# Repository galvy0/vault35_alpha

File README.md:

# Vault35 Alpha Stagger PCB
Alpha stagger version of Cain's Vault35 keyboard.  
Check out the original product and other awesome projects of Cain at [https://mechvault.net/](https://mechvault.net/).  

## PCB
### Layout Options

### Middle Column Options
There are four options to fill in the space in the middle column: 1) two normal switches, 2) two encoders (or a combination of encoders and normal switches), 3) an OLED, and 4) a trackpoint module.  
For TP option, refer to my phoenix45 alpha stagger repo: https://github.com/galvy0/phoenix45_alpha

## Firmware
https://github.com/galvy0/qmk_firmware/tree/galvy/keyboards/galvy/vault35_alpha

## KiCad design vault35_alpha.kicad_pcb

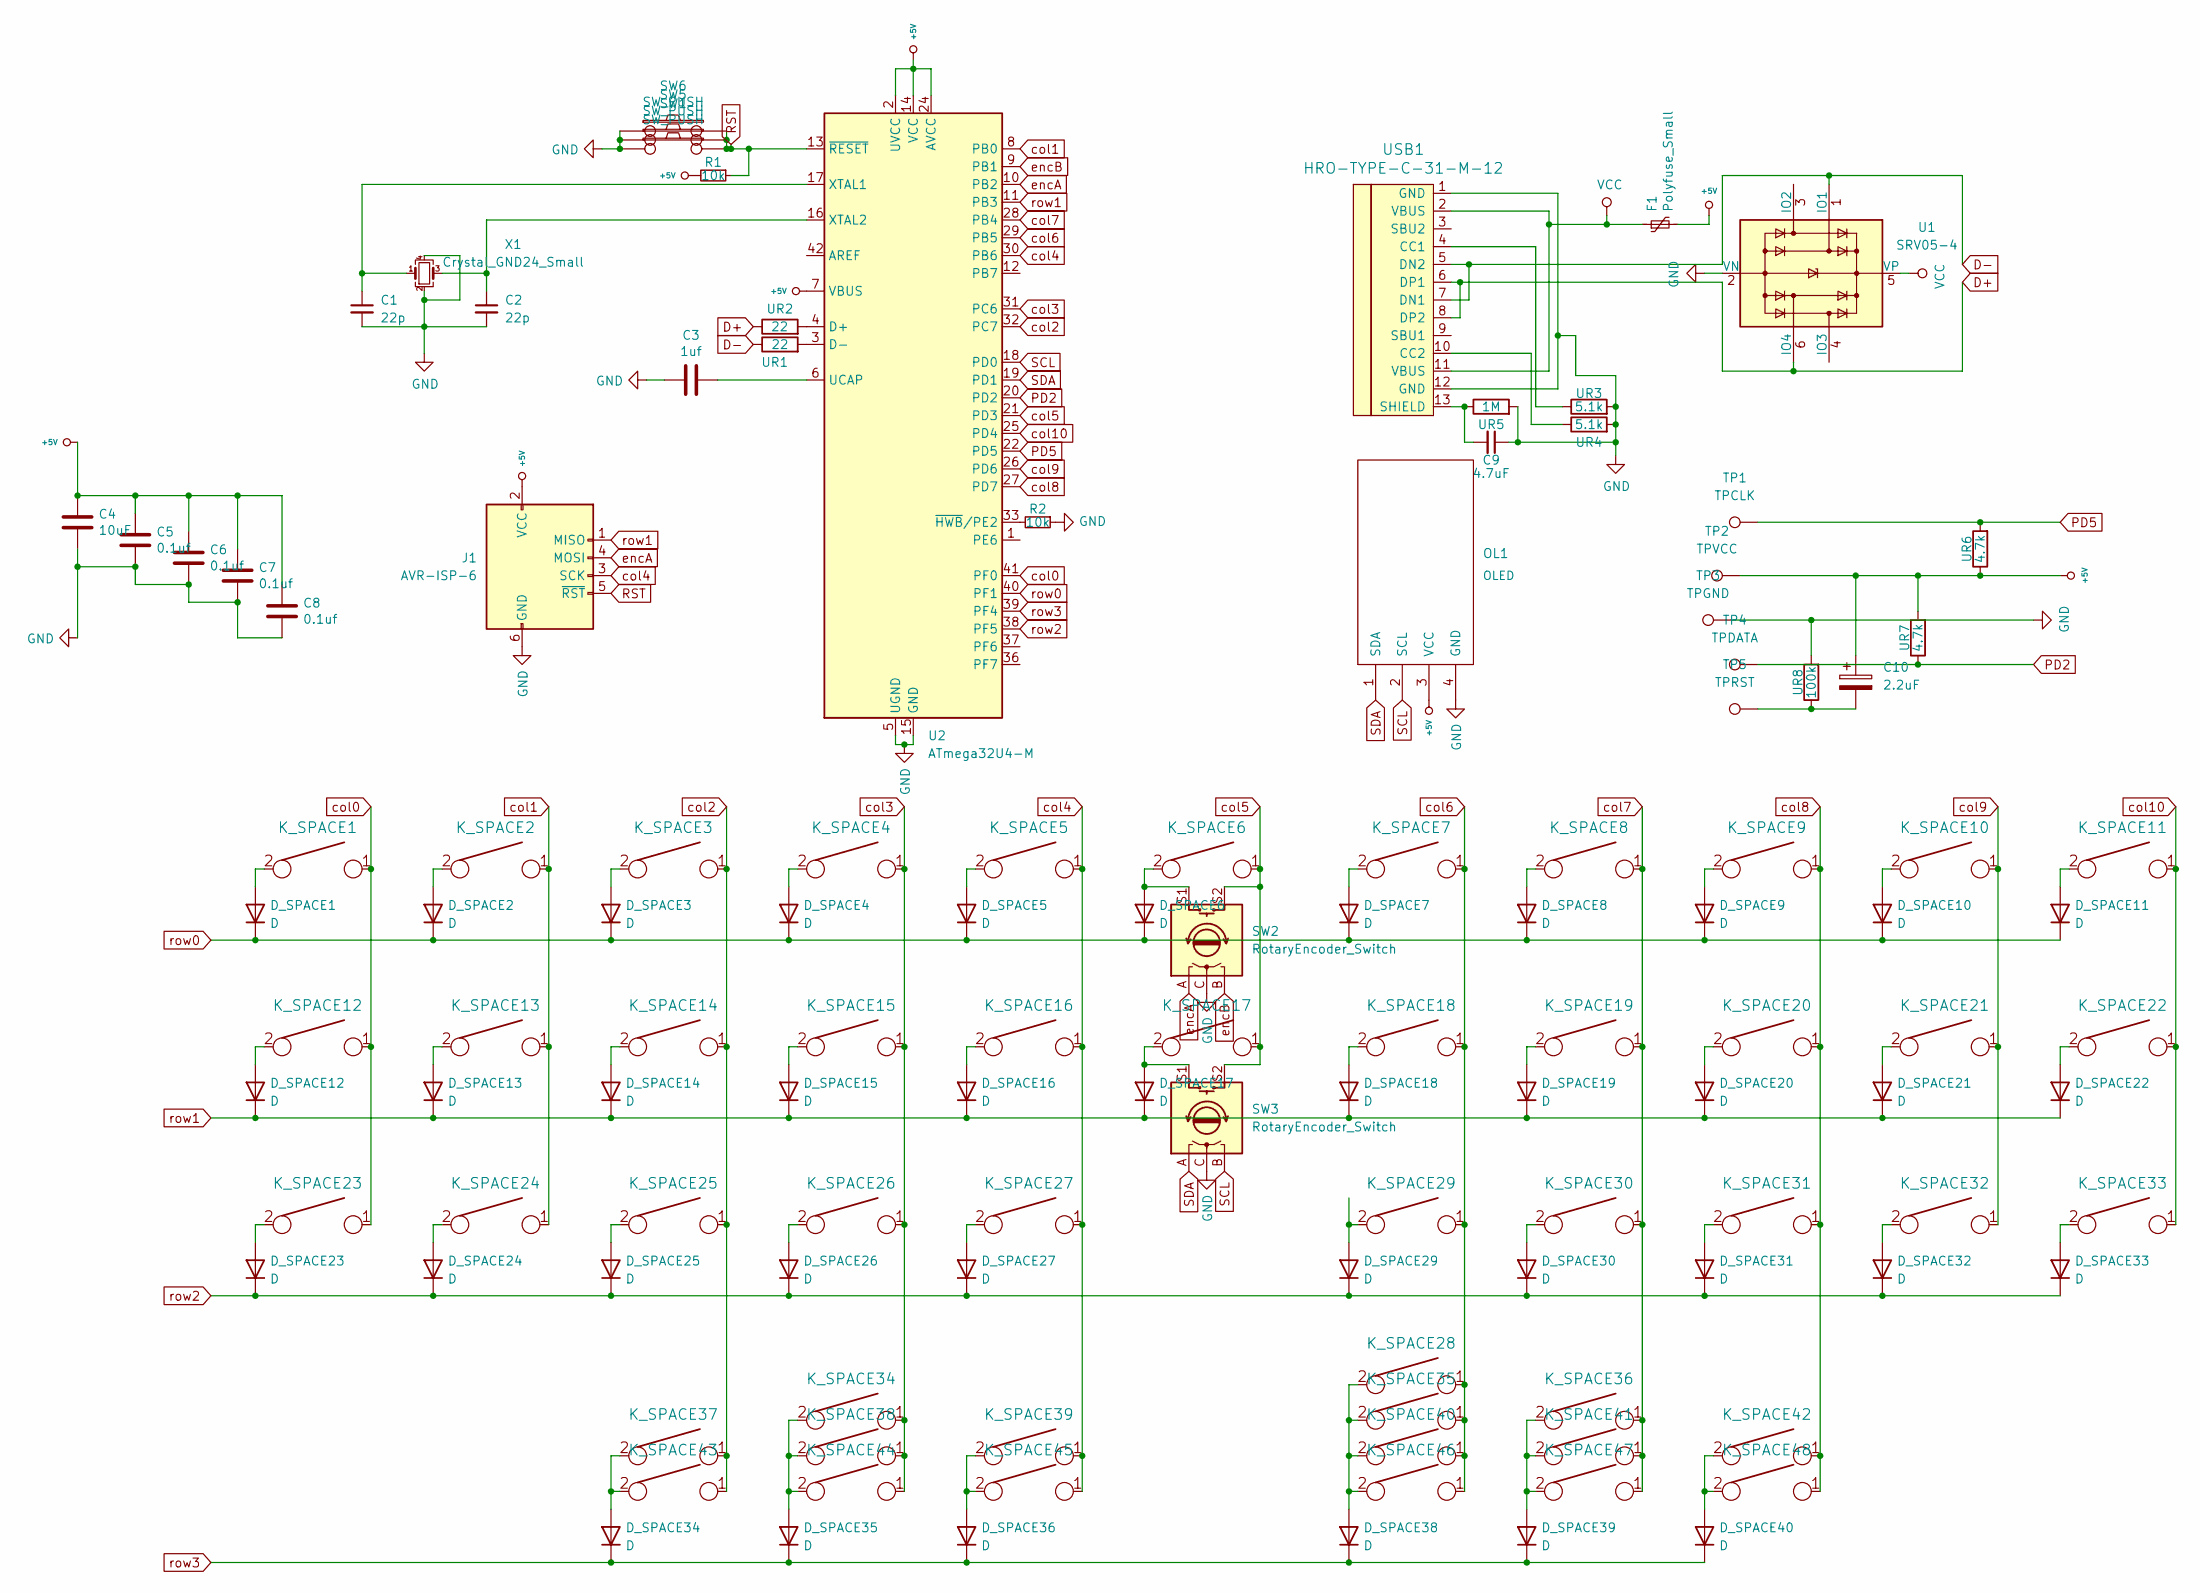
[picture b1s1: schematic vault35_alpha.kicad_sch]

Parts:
C1, C2: 22p; C_0805_2012Metric
C3: 1uf; C_0805_2012Metric
C4: 10uF; C_0805_2012Metric
C5, C6, C7, C8: 0.1uf; C_0805_2012Metric
C9: 4.7uF; C_0805_2012Metric
C10: 2.2uF; C_0805_2012Metric_Pad1.18x1.45mm_HandSolder
D_SPACE1, D_SPACE2, D_SPACE3, D_SPACE4, D_SPACE5, D_SPACE6, D_SPACE7, D_SPACE8, D_SPACE9, D_SPACE10, D_SPACE11, D_SPACE12, D_SPACE13, D_SPACE14, D_SPACE15, D_SPACE16, D_SPACE17, D_SPACE18, D_SPACE19, D_SPACE20, D_SPACE21, D_SPACE22, D_SPACE23, D_SPACE24, D_SPACE25, D_SPACE26, D_SPACE27, D_SPACE29, D_SPACE30, D_SPACE31, D_SPACE32, D_SPACE33, D_SPACE34, D_SPACE35, D_SPACE36, D_SPACE38, D_SPACE39, D_SPACE40: D; D_SOD-123
F1: Polyfuse_Small; Fuse_1206_3216Metric_Pad1.42x1.75mm_HandSolder
J1: AVR-ISP-6; IDC-Header_2x03_P2.54mm_Vertical
K_SPACE1, K_SPACE2, K_SPACE3, K_SPACE4, K_SPACE5, K_SPACE6, K_SPACE7, K_SPACE8, K_SPACE9, K_SPACE10, K_SPACE11, K_SPACE12, K_SPACE13, K_SPACE14, K_SPACE15, K_SPACE16, K_SPACE17, K_SPACE18, K_SPACE19, K_SPACE20, K_SPACE21, K_SPACE22, K_SPACE24, K_SPACE25, K_SPACE26, K_SPACE27, K_SPACE29, K_SPACE30, K_SPACE31, K_SPACE32, K_SPACE43, K_SPACE44, K_SPACE47, K_SPACE48: KEYSW; MXOnly-1U-NoLED
K_SPACE23, K_SPACE28, K_SPACE33, K_SPACE39: KEYSW; MXOnly-1.5U-NoLED
K_SPACE34, K_SPACE36, K_SPACE37, K_SPACE38, K_SPACE41, K_SPACE42: KEYSW; MXOnly-1.25U-NoLED
K_SPACE35, K_SPACE45: KEYSW; MXOnly-1.75U-NoLED
K_SPACE40: KEYSW; MXOnly-3U-ReversedStabilizers-NoSwitch
K_SPACE46: KEYSW; MXOnly-6U-Centered-ReversedStabilizers-NoLED
OL1: OLED; OLED_v2
R1, R2: 10k; R_0805_2012Metric
SW1, SW6: SW_PUSH; SW_SPST_SKQG_WithoutStem
SW2, SW3: RotaryEncoder_Switch; RotaryEncoder_Alps_EC11E-Switch_Vertical_H20mm
SW5: SW_PUSH; PinHeader_1x02_P2.54mm_Vertical
TP1: TPCLK; TestPoint_THTPad_1.0x1.0mm_Drill0.5mm
TP2: TPVCC; TestPoint_THTPad_1.0x1.0mm_Drill0.5mm
TP3: TPGND; TestPoint_THTPad_1.0x1.0mm_Drill0.5mm
TP4: TPDATA; TestPoint_THTPad_1.0x1.0mm_Drill0.5mm
TP5: TPRST; TestPoint_THTPad_1.0x1.0mm_Drill0.5mm
U1: SRV05-4; SOT-23-6
U2: ATmega32U4-M; QFN-44-1EP_7x7mm_P0.5mm_EP5.2x5.2mm_ThermalVias
UR1, UR2: 22; R_0805_2012Metric
UR3, UR4: 5.1k; R_0805_2012Metric
UR5: 1M; R_0805_2012Metric
UR6, UR7: 4.7k; R_0805_2012Metric_Pad1.20x1.40mm_HandSolder
UR8: 100k; R_0805_2012Metric_Pad1.20x1.40mm_HandSolder
USB1: HRO-TYPE-C-31-M-12; HRO-TYPE-C-31-M-12-HandSoldering
X1: Crystal_GND24_Small; Crystal_SMD_3225-4Pin_3.2x2.5mm_HandSoldering

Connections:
+5V: C4.1, C5.1, C6.1, C7.1, C8.1, C10.1, F1.2, J1.2 (VCC), OL1.3 (VCC), R1.2, TP2.1, U2.2 (UVCC), U2.7 (VBUS), U2.14 (VCC), U2.24 (AVCC), U2.34 (VCC), U2.44 (AVCC), UR6.1, UR7.2
D+: U1.6 (IO4), UR1.1, USB1.6 (DP1), USB1.8 (DP2)
D-: U1.1 (IO1), UR2.1, USB1.5 (DN2), USB1.7 (DN1)
GND: C1.2, C2.2, C3.2, C4.2, C5.2, C6.2, C7.2, C8.2, C9.1, J1.6 (GND), OL1.4 (GND), R2.1, SW1.1, SW2.C, SW3.C, SW5.1, SW6.1, TP3.1, U1.2 (VN), U2.5 (UGND), U2.15 (GND), U2.23 (GND), U2.35 (GND), U2.43 (GND), U2.45 (GND), UR3.2, UR4.2, UR5.2, UR8.2, USB1.1 (GND), USB1.12 (GND), X1.2, X1.4
unnamed: C1.1, U2.17 (XTAL1), X1.1
unnamed: C2.1, U2.16 (XTAL2), X1.3
unnamed: C3.1, U2.6 (UCAP)
unnamed: C9.2, UR5.1, USB1.13 (SHIELD)
unnamed: C10.2, TP5.1, UR8.1
unnamed: D_SPACE1.2 (A), K_SPACE1.2
unnamed: D_SPACE2.2 (A), K_SPACE2.2
unnamed: D_SPACE3.2 (A), K_SPACE3.2
unnamed: D_SPACE4.2 (A), K_SPACE4.2
unnamed: D_SPACE5.2 (A), K_SPACE5.2
unnamed: D_SPACE6.2 (A), K_SPACE6.2, SW2.S1
unnamed: D_SPACE7.2 (A), K_SPACE7.2
unnamed: D_SPACE8.2 (A), K_SPACE8.2
unnamed: D_SPACE9.2 (A), K_SPACE9.2
unnamed: D_SPACE10.2 (A), K_SPACE10.2
unnamed: D_SPACE11.2 (A), K_SPACE11.2
unnamed: D_SPACE12.2 (A), K_SPACE12.2
unnamed: D_SPACE13.2 (A), K_SPACE13.2
unnamed: D_SPACE14.2 (A), K_SPACE14.2
unnamed: D_SPACE15.2 (A), K_SPACE15.2
unnamed: D_SPACE16.2 (A), K_SPACE16.2
unnamed: D_SPACE17.2 (A), K_SPACE17.2, SW3.S1
unnamed: D_SPACE18.2 (A), K_SPACE18.2
unnamed: D_SPACE19.2 (A), K_SPACE19.2
unnamed: D_SPACE20.2 (A), K_SPACE20.2
unnamed: D_SPACE21.2 (A), K_SPACE21.2
unnamed: D_SPACE22.2 (A), K_SPACE22.2
unnamed: D_SPACE23.2 (A), K_SPACE23.2
unnamed: D_SPACE24.2 (A), K_SPACE24.2
unnamed: D_SPACE25.2 (A), K_SPACE25.2
unnamed: D_SPACE26.2 (A), K_SPACE26.2
unnamed: D_SPACE27.2 (A), K_SPACE27.2
unnamed: D_SPACE29.2 (A), K_SPACE29.2
unnamed: D_SPACE30.2 (A), K_SPACE30.2
unnamed: D_SPACE31.2 (A), K_SPACE31.2
unnamed: D_SPACE32.2 (A), K_SPACE32.2
unnamed: D_SPACE33.2 (A), K_SPACE33.2
unnamed: D_SPACE34.2 (A), K_SPACE37.2, K_SPACE43.2
unnamed: D_SPACE35.2 (A), K_SPACE34.2, K_SPACE38.2, K_SPACE44.2
unnamed: D_SPACE36.2 (A), K_SPACE39.2, K_SPACE45.2
unnamed: D_SPACE38.2 (A), K_SPACE28.2, K_SPACE35.2, K_SPACE40.2, K_SPACE46.2
unnamed: D_SPACE39.2 (A), K_SPACE36.2, K_SPACE41.2, K_SPACE47.2
unnamed: D_SPACE40.2 (A), K_SPACE42.2, K_SPACE48.2
unnamed: R2.2, U2.33 (~HWB/PE2)
unnamed: U2.3 (D-), UR2.2
unnamed: U2.4 (D+), UR1.2
unnamed: UR3.1, USB1.4 (CC1)
unnamed: UR4.1, USB1.10 (CC2)
PD2: TP4.1, U2.20 (PD2), UR7.1
PD5: TP1.1, U2.22 (PD5), UR6.2
RST: J1.5 (~RST), R1.1, SW1.2, SW5.2, SW6.2, U2.13 (~RESET)
SCL: OL1.2 (SCL), SW3.B, U2.18 (PD0)
SDA: OL1.1 (SDA), SW3.A, U2.19 (PD1)
VCC: F1.1, U1.5 (VP), USB1.2 (VBUS), USB1.11 (VBUS)
col0: K_SPACE1.1, K_SPACE12.1, K_SPACE23.1, U2.41 (PF0)
col1: K_SPACE2.1, K_SPACE13.1, K_SPACE24.1, U2.8 (PB0)
col2: K_SPACE3.1, K_SPACE14.1, K_SPACE25.1, K_SPACE37.1, K_SPACE43.1, U2.32 (PC7)
col3: K_SPACE4.1, K_SPACE15.1, K_SPACE26.1, K_SPACE34.1, K_SPACE38.1, K_SPACE44.1, U2.31 (PC6)
col4: J1.3 (SCK), K_SPACE5.1, K_SPACE16.1, K_SPACE27.1, K_SPACE39.1, K_SPACE45.1, U2.30 (PB6)
col5: K_SPACE6.1, K_SPACE17.1, SW2.S2, SW3.S2, U2.21 (PD3)
col6: K_SPACE7.1, K_SPACE18.1, K_SPACE28.1, K_SPACE29.1, K_SPACE35.1, K_SPACE40.1, K_SPACE46.1, U2.29 (PB5)
col7: K_SPACE8.1, K_SPACE19.1, K_SPACE30.1, K_SPACE36.1, K_SPACE41.1, K_SPACE47.1, U2.28 (PB4)
col8: K_SPACE9.1, K_SPACE20.1, K_SPACE31.1, K_SPACE42.1, K_SPACE48.1, U2.27 (PD7)
col9: K_SPACE10.1, K_SPACE21.1, K_SPACE32.1, U2.26 (PD6)
col10: K_SPACE11.1, K_SPACE22.1, K_SPACE33.1, U2.25 (PD4)
encA: J1.4 (MOSI), SW2.A, U2.10 (PB2)
encB: SW2.B, U2.9 (PB1)
row0: D_SPACE1.1 (K), D_SPACE2.1 (K), D_SPACE3.1 (K), D_SPACE4.1 (K), D_SPACE5.1 (K), D_SPACE6.1 (K), D_SPACE7.1 (K), D_SPACE8.1 (K), D_SPACE9.1 (K), D_SPACE10.1 (K), D_SPACE11.1 (K), U2.40 (PF1)
row1: D_SPACE12.1 (K), D_SPACE13.1 (K), D_SPACE14.1 (K), D_SPACE15.1 (K), D_SPACE16.1 (K), D_SPACE17.1 (K), D_SPACE18.1 (K), D_SPACE19.1 (K), D_SPACE20.1 (K), D_SPACE21.1 (K), D_SPACE22.1 (K), J1.1 (MISO), U2.11 (PB3)
row2: D_SPACE23.1 (K), D_SPACE24.1 (K), D_SPACE25.1 (K), D_SPACE26.1 (K), D_SPACE27.1 (K), D_SPACE29.1 (K), D_SPACE30.1 (K), D_SPACE31.1 (K), D_SPACE32.1 (K), D_SPACE33.1 (K), U2.38 (PF5)
row3: D_SPACE34.1 (K), D_SPACE35.1 (K), D_SPACE36.1 (K), D_SPACE38.1 (K), D_SPACE39.1 (K), D_SPACE40.1 (K), U2.39 (PF4)

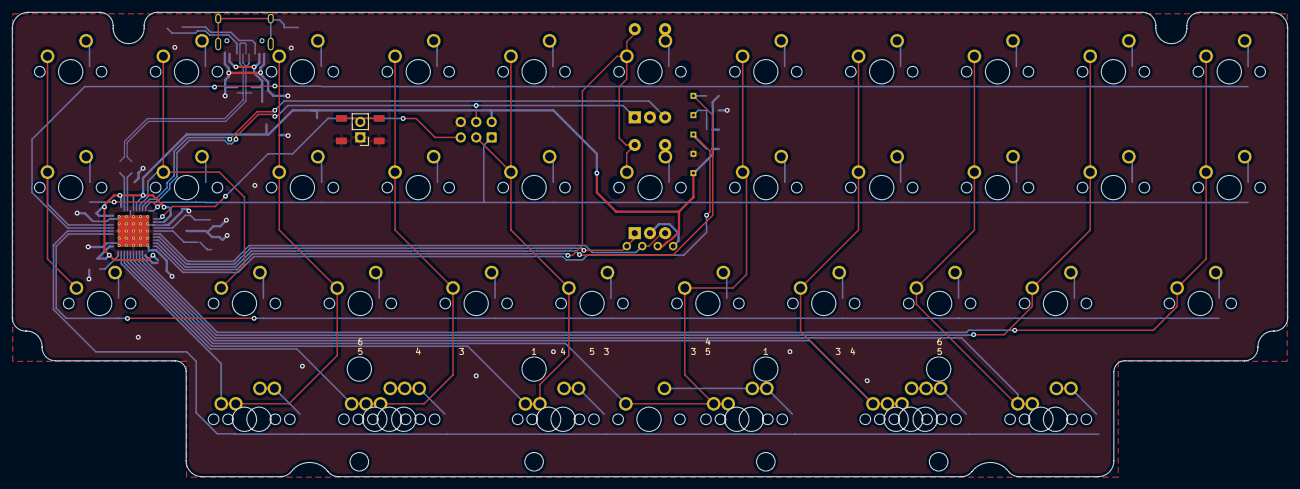
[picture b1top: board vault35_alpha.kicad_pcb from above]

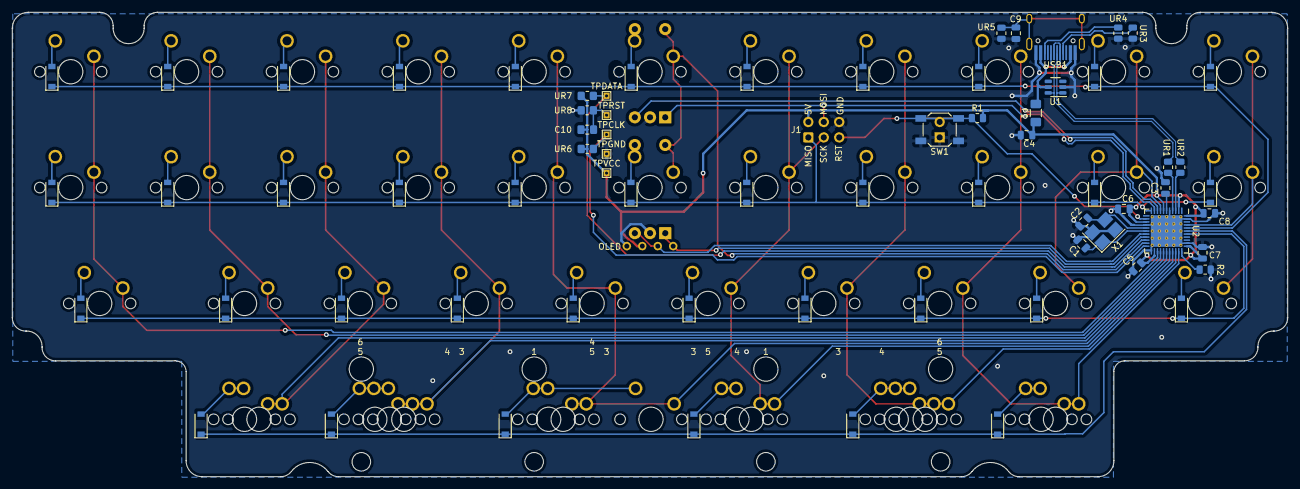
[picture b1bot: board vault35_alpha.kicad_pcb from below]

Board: 2 copper layers, 209.7 x 76.4 mm, 123 parts (70 on the bottom side), 75 nets.

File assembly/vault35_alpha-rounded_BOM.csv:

sep=;
"Id";"Designator";"Package";"Quantity";"Designation";"Supplier and ref";
1;"K_SPACE4,K_SPACE17,K_SPACE30,K_SPACE9,K_SPACE21,K_SPACE15,K_SPACE44,K_SPACE10,K_SPACE2,K_SPACE47,K_SPACE14,K_SPACE32,K_SPACE26,K_SPACE25,K_SPACE8,K_SPACE43,K_SPACE20,K_SPACE48,K_SPACE11,K_SPACE19,K_SPACE16,K_SPACE12,K_SPACE22,K_SPACE3,K_SPACE7,K_SPACE6,K_SPACE29,K_SPACE5,K_SPACE27,K_SPACE24,K_SPACE18,K_SPACE31,K_SPACE1,K_SPACE13";"MXOnly-1U-NoLED";34;"KEYSW";;;
2;"SW5";"PinHeader_1x02_P2.54mm_Vertical";1;"SW_PUSH";;;
3;"K_SPACE28,K_SPACE33,K_SPACE39,K_SPACE23";"MXOnly-1.5U-NoLED";4;"KEYSW";;;
4;"K_SPACE37,K_SPACE41,K_SPACE34,K_SPACE36,K_SPACE38,K_SPACE42";"MXOnly-1.25U-NoLED";6;"KEYSW";;;
5;"K_SPACE40";"MXOnly-3U-ReversedStabilizers-NoSwitch";1;"KEYSW";;;
6;"SW2,SW3";"RotaryEncoder_Alps_EC11E-Switch_Vertical_H20mm";2;"RotaryEncoder_Switch";;;
7;"SW6,SW1";"SW_SPST_SKQG_WithoutStem";2;"SW_PUSH";;;
8;"K_SPACE45,K_SPACE35";"MXOnly-1.75U-NoLED";2;"KEYSW";;;
9;"K_SPACE46";"MXOnly-6U-Centered-ReversedStabilizers-NoLED";1;"KEYSW";;;
10;"OL1";"OLED_v2";1;"OLED";;;
11;"D_SPACE17,D_SPACE34,D_SPACE5,D_SPACE1,D_SPACE32,D_SPACE36,D_SPACE38,D_SPACE25,D_SPACE18,D_SPACE9,D_SPACE13,D_SPACE35,D_SPACE12,D_SPACE29,D_SPACE2,D_SPACE20,D_SPACE24,D_SPACE21,D_SPACE15,D_SPACE26,D_SPACE16,D_SPACE14,D_SPACE30,D_SPACE4,D_SPACE11,D_SPACE10,D_SPACE40,D_SPACE8,D_SPACE39,D_SPACE3,D_SPACE27,D_SPACE23,D_SPACE31,D_SPACE7,D_SPACE33,D_SPACE19,D_SPACE22,D_SPACE6";"D_SOD-123";38;"D";;;
12;"X1";"Crystal_SMD_3225-4Pin_3.2x2.5mm_HandSoldering";1;"Crystal_GND24_Small";;;
13;"TP1";"TestPoint_THTPad_1.0x1.0mm_Drill0.5mm";1;"TPCLK";;;
14;"U1";"SOT-23-6";1;"SRV05-4";;;
15;"UR5";"R_0805_2012Metric";1;"1M";;;
16;"F1";"Fuse_1206_3216Metric_Pad1.42x1.75mm_HandSolder";1;"Polyfuse_Small";;;
17;"TP4";"TestPoint_THTPad_1.0x1.0mm_Drill0.5mm";1;"TPDATA";;;
18;"UR3,UR4";"R_0805_2012Metric";2;"5.1k";;;
19;"U2";"QFN-44-1EP_7x7mm_P0.5mm_EP5.2x5.2mm_ThermalVias";1;"ATmega32U4-M";;;
20;"C2,C1";"C_0805_2012Metric";2;"22p";;;
21;"C4";"C_0805_2012Metric";1;"10uF";;;
22;"C10";"C_0805_2012Metric_Pad1.18x1.45mm_HandSolder";1;"2.2uF";;;
23;"TP2";"TestPoint_THTPad_1.0x1.0mm_Drill0.5mm";1;"TPVCC";;;
24;"TP3";"TestPoint_THTPad_1.0x1.0mm_Drill0.5mm";1;"TPGND";;;
25;"UR1,UR2";"R_0805_2012Metric";2;"22";;;
26;"R2,R1";"R_0805_2012Metric";2;"10k";;;
27;"TP5";"TestPoint_THTPad_1.0x1.0mm_Drill0.5mm";1;"TPRST";;;
28;"UR8";"R_0805_2012Metric_Pad1.20x1.40mm_HandSolder";1;"100k";;;
29;"C6,C8,C5,C7";"C_0805_2012Metric";4;"0.1uf";;;
30;"UR7,UR6";"R_0805_2012Metric_Pad1.20x1.40mm_HandSolder";2;"4.7k";;;
31;"C3";"C_0805_2012Metric";1;"1uf";;;
32;"C9";"C_0805_2012Metric";1;"4.7uF";;;
33;"USB1";"HRO-TYPE-C-31-M-12-HandSoldering";1;"HRO-TYPE-C-31-M-12";;;
34;"J1";"IDC-Header_2x03_P2.54mm_Vertical";1;"AVR-ISP-6";;;

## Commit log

2022-07-15 init alpha design
2022-09-18 update with TP, alpha stagger
2022-09-23 production
2022-09-25 layouts
2022-09-25 update options
2022-10-28 Update Plates
2022-10-28 update kle image
